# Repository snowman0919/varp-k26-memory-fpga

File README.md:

# 온디바이스 sLLM을 위한 K26–Memory FPGA 후보 구조

Kria K26이 연산·제어를 맡고 외부 Memory FPGA가 다채널로 가중치를 공급하는
확장형 가속기 구조를 설계하고, 데이터 이동 비용을 포함한 작업 재분배가 언제
유효한지 평가한 연구 저장소다.

## 핵심 결론

- Gemma 3 1B INT8와 문맥 길이 32K의 용량 모델은 2.43 GiB다. 따라서 기본 선택은
  K26 로컬이며 외부 8GB는 더 큰 모델·긴 문맥·로컬 경합을 위한 확장 후보다.
- 실제 그래프의 토큰당 183개 투영을 의존성 있는 802개 TileJob으로 변환했다.
- 합성 편향 부하의 동일 시드 다섯 개 중앙값에서 S3는 S1보다 TileJob p95를
  19.13%, p99를 18.71% 줄였다. 반면 Gemma 기존 산술 배치에서는 p95가 0.28%
  늘어 정책 효과가 초기 배치와 이동 비용에 조건부임을 확인했다.
- 대표 실제 가중치 타일 세 개가 작업 수락→DMA 요청→DDR 응답 경계→논리 링크
  FIFO→MatVec 결과의 폐루프 논리 RTL을 통과했고 INT32 기준과 일치했다.

이 수치는 보드 실측이 아니다. GTH·MIG 물리 타이밍, 전체 보드 전력·가격,
제작 가능한 PCB는 아직 검증하지 않았다.

## 연구 기여

1. K26의 연산·제어와 Memory FPGA의 가중치 공급 역할을 분리한 확장 후보 구조
2. 원격 가중치·활성값·부분합 비용을 서비스 시간에 부과한 동적 작업 배치 평가
3. 실제 모델 형상→분석 모델→폐루프 논리 RTL→KiCad 라우팅 쿠폰의 재현 흐름

## 빠른 시작

필수 도구는 Python 3.11+, Java 21, sbt, Verilator, KiCad CLI, Pandoc,
Chromium, Poppler, ffmpeg, Manim과 한글 글꼴이다.

```bash
make setup
make test
make rtl-test
make paper-experiments
make research-freeze
make paper
make presentation
make reproduce
```

허가된 원본 Gemma 3 1B ONNX가 있을 때만 다음 명령으로 trace를 재생성한다.
모델 가중치는 저장소와 release에 포함하지 않는다.

```bash
GEMMA3_1B_ONNX_DIR=/authorized/path make model-trace
```

## 주요 산출물

- [제출 논문](paper/final/submission_manuscript.pdf)
- [기술보고서](paper/technical_report/technical_report.pdf)
- [17장 본선 발표자료](presentation/final/presentation.pptx)
- [발표 PDF](presentation/final/presentation.pdf)
- [발표자 노트](presentation/final/speaker_notes.md)
- [슬라이드별 출처 인덱스](presentation/final/slide_source_index.md)
- [발표 contact sheet](presentation/final/slide_contact_sheet.png)
- [연구 동결 기록](research/v11_research_freeze.md)
- [스터디팩과 Q&A](study/README.md)
- [코드·자료 공개 안내](paper/final/code_and_data_availability.md)
- [학술대회 패키지 통합 인덱스](conference_package/INDEX.md)

## 저장소 구조

| 경로 | 내용 |
|---|---|
| `src/`, `tests/` | 의존성 인식 분석 모델과 검증 |
| `hw/` | SpinalHDL/Verilator RTL과 폐루프 논리 가상 시제품 |
| `experiments/`, `results/`, `evidence/` | Gemma trace, 합성 실험, 결과 CSV |
| `hardware/kicad/` | 일반 경계 라우팅 쿠폰, **NOT FOR FABRICATION** |
| `paper/`, `presentation/`, `study/` | 논문·발표·방어 자료 |

## 재현과 주장 범위

`make research-freeze`는 동일 시드 비교, 원격 복사 비용 부과, Gemma 단계·토큰
의존성, 실제 타일 RTL trace, K26 로컬 기준선과 KiCad 범위를 검사한다. 자세한
논리/물리 경계는 [architecture.md](docs/architecture.md)를 따른다.

## 소스 아카이브

GitHub의 자동 **Download ZIP**은 저장소 tree를 그대로 받는 편의 경로다. 재현
기준은 `v11-conference-final` release에 첨부하는 공식
`VARP_K26_Source.zip`이며, 이 파일은 `source_manifest`와 checksum을 함께
포함한다. 두 경로 모두 모델 가중치는 포함하지 않는다.

## 인용과 라이선스

[CITATION.cff](CITATION.cff)의 최윤혁(한국디지털미디어고등학교,
[ORCID 0009-0006-3537-0249](https://orcid.org/0009-0006-3537-0249)) 정보를 사용한다.
소스 사용 조건은 [LICENSE](LICENSE)를 따른다.

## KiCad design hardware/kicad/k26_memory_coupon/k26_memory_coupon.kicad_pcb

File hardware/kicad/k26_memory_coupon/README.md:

# K26 memory/interface validation coupon

> **NOT FOR FABRICATION — proposal_only**

This electrically connected KiCad 9 coupon accounts for one DDR3L x16
representative channel slice, a four-lane full-duplex K26 PL-GTH link bundle,
two K26 GTH reference-clock inputs, reset/config/JTAG, and a decoupling subset.

The XC7K160T and K26 are connector/bank boundaries. No XC7K160T FFG676 ball,
MIG placement, production stackup, impedance, or timing claim is made.

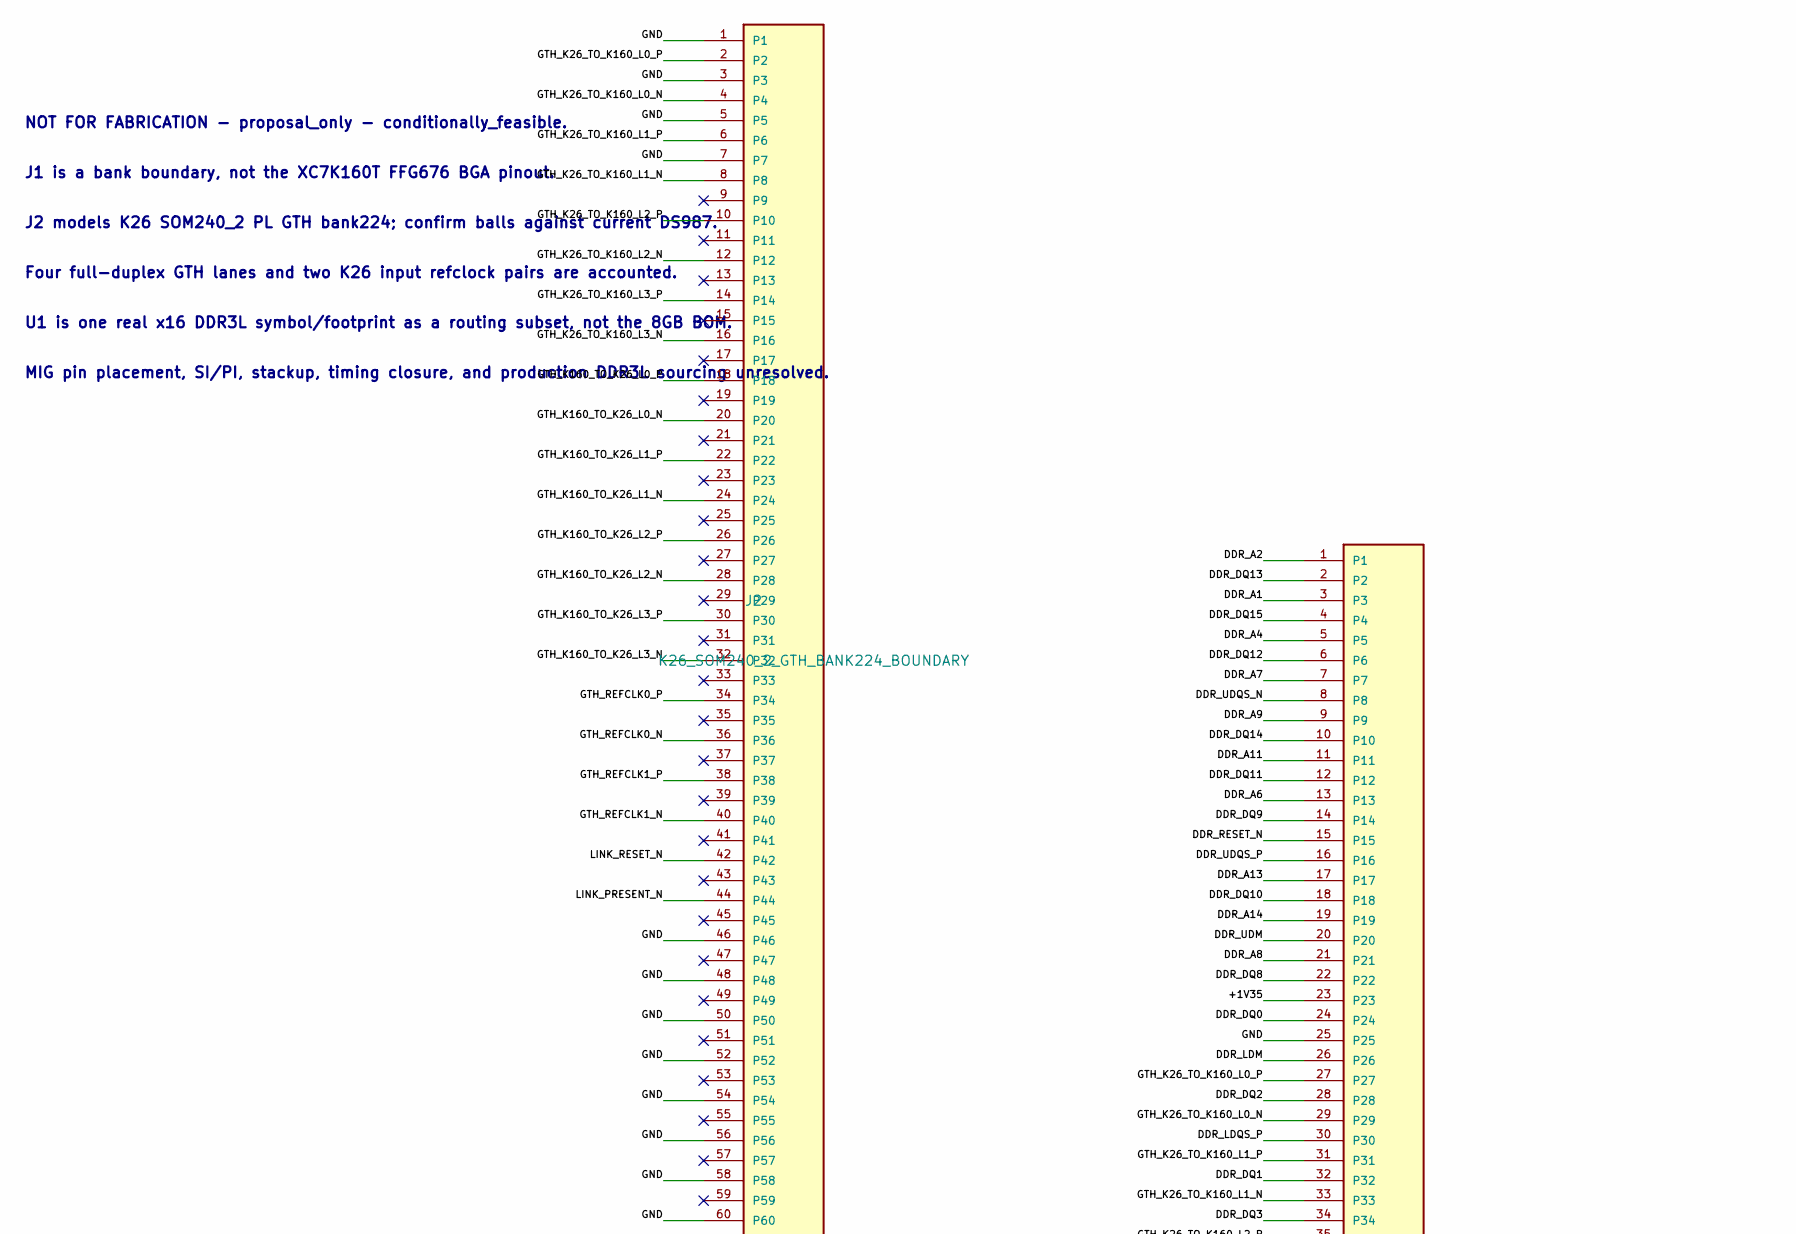
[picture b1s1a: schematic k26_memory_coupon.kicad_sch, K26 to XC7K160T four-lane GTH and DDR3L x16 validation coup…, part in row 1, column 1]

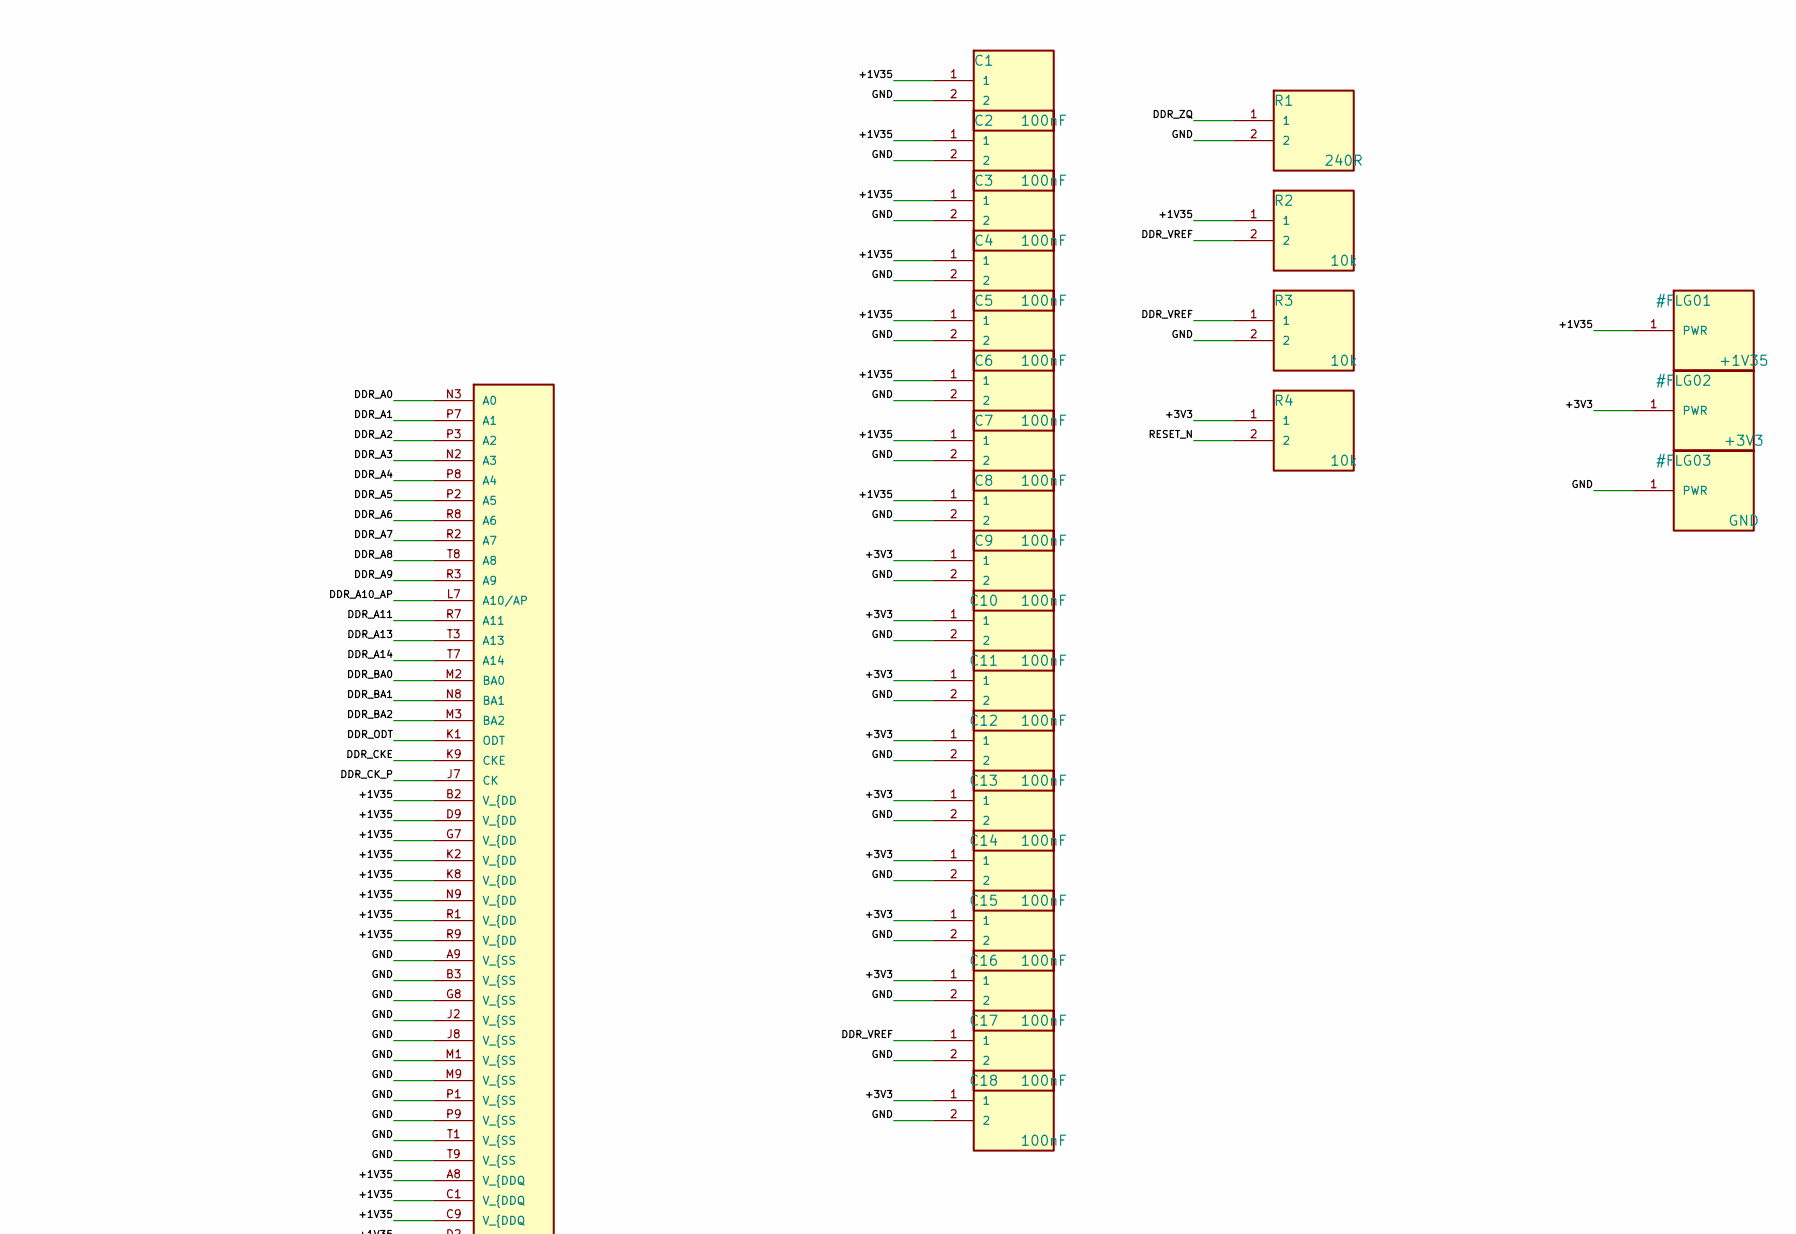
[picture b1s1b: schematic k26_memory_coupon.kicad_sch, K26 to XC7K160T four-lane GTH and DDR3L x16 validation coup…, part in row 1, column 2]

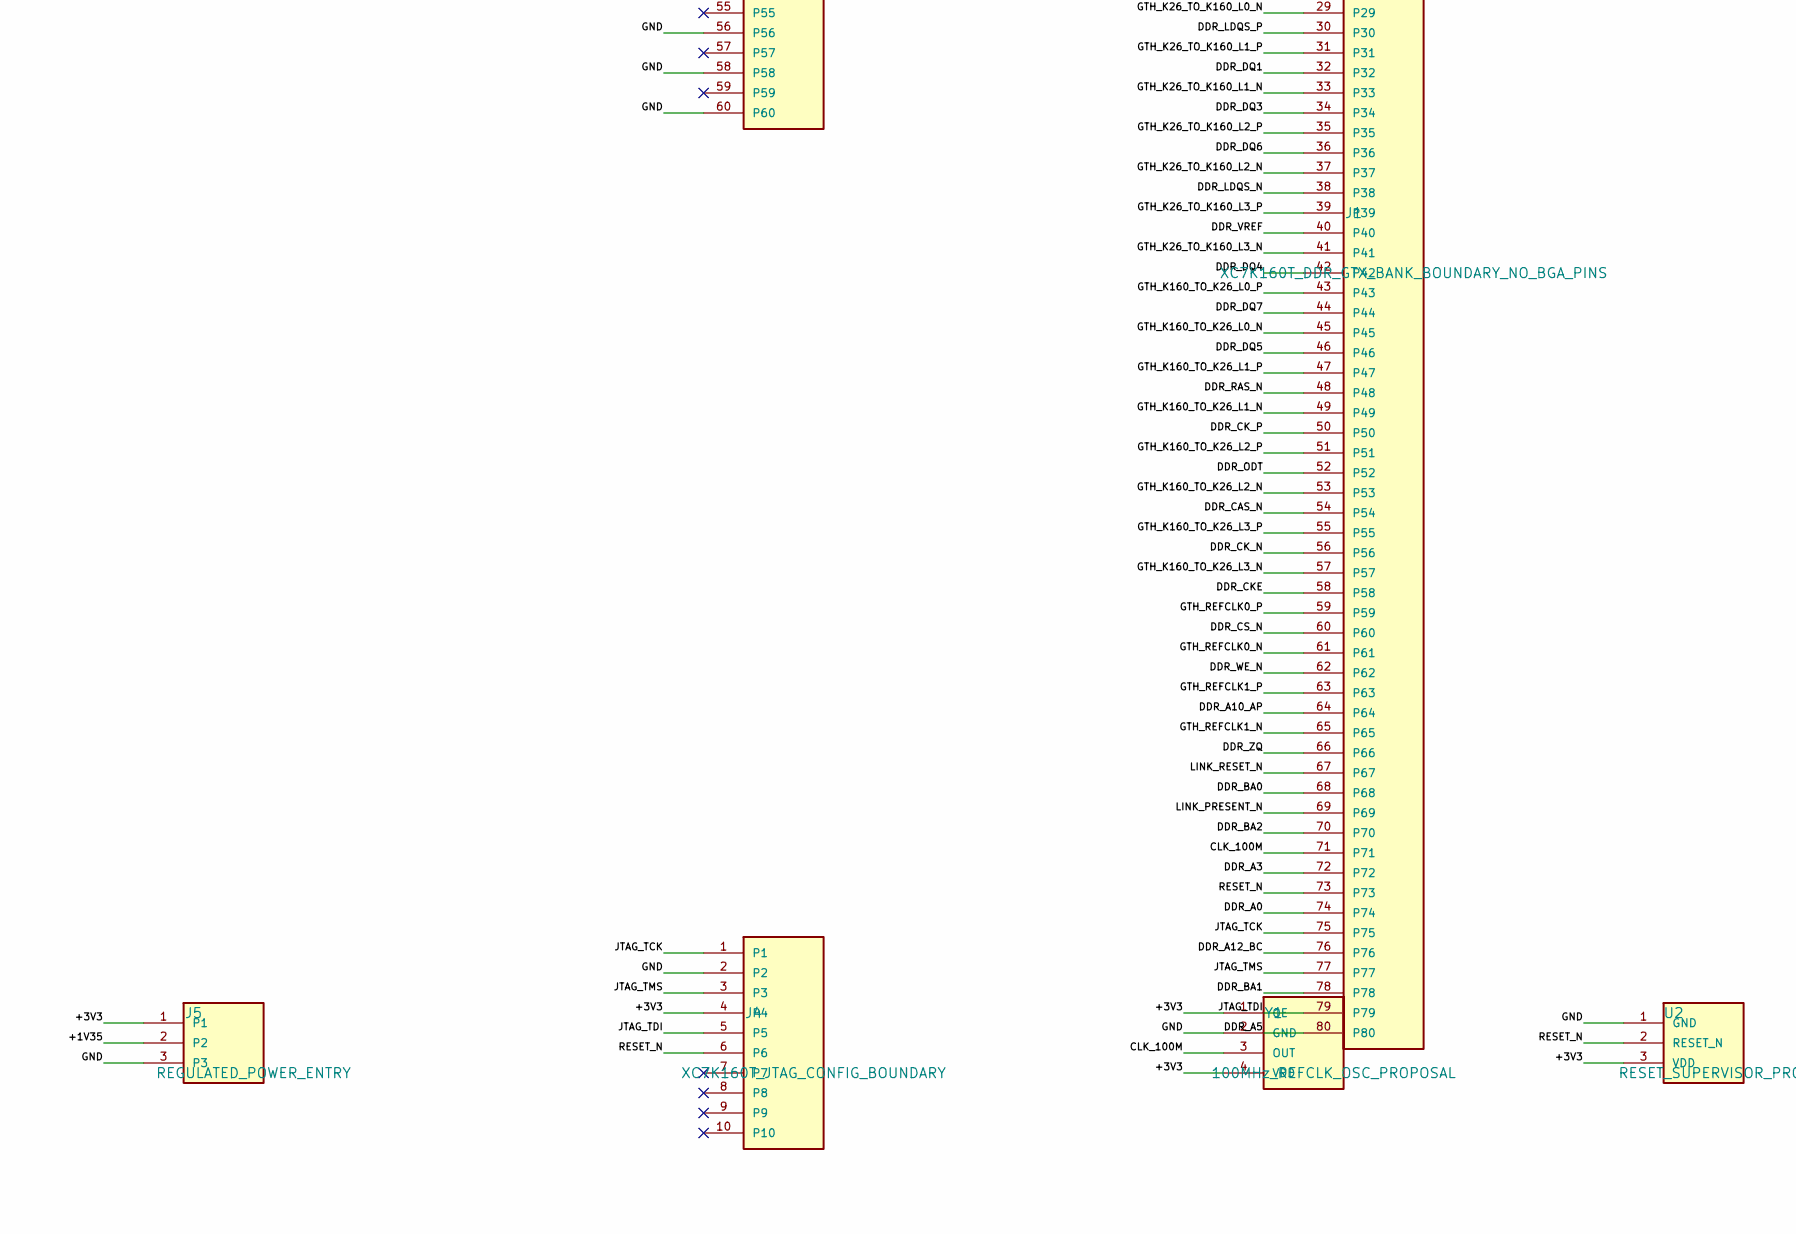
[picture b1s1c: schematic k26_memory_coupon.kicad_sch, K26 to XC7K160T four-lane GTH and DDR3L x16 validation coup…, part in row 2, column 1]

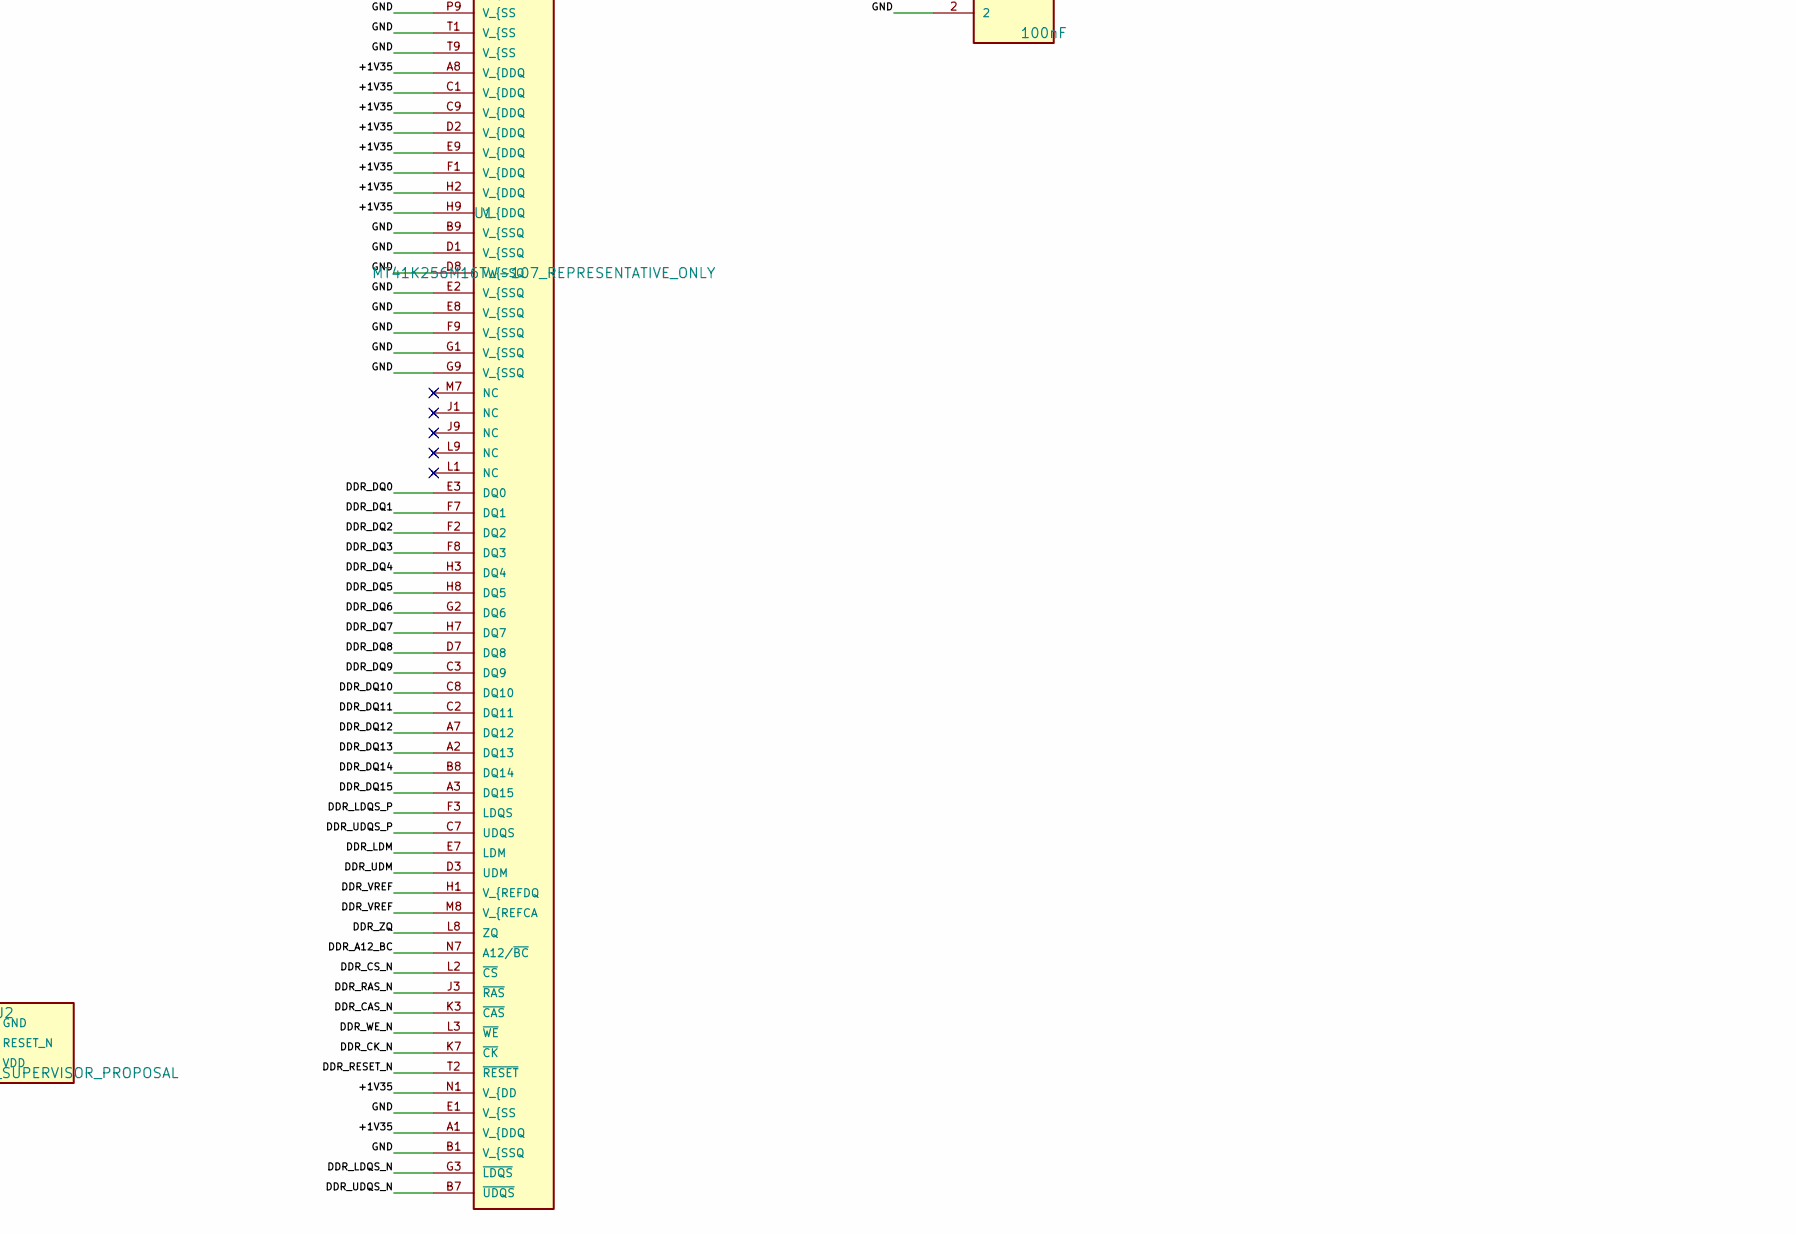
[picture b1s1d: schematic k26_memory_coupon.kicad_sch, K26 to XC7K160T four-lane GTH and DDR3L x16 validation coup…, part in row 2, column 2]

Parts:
C1, C2, C3, C4, C5, C6, C7, C8, C9, C10, C11, C12, C13, C14, C15, C16, C17, C18: 100nF; C_0402_1005Metric
J1: XC7K160T_DDR_GTX_BANK_BOUNDARY_NO_BGA_PINS; Samtec_HSEC8-140-03-X-DV_2x40_P0.8mm_Pol22_Socket
J2: K26_SOM240_2_GTH_BANK224_BOUNDARY; Samtec_HSEC8-130-03-X-DV_2x30_P0.8mm_Socket
J4: XC7K160T_JTAG_CONFIG_BOUNDARY; PinHeader_2x05_P1.27mm_Vertical
J5: REGULATED_POWER_ENTRY; TerminalBlock_Phoenix_MKDS-1,5-3_1x03_P5.00mm_Horizontal
R1: 240R; R_0402_1005Metric
R2, R3, R4: 10k; R_0402_1005Metric
U1: MT41K256M16TW-107_REPRESENTATIVE_ONLY; Micron_FBGA-96_8x14mm_Layout9x16_P0.8mm; MPN MT41K256M16TW-107
U2: RESET_SUPERVISOR_PROPOSAL; SOT-23
Y1: 100MHz_REFCLK_OSC_PROPOSAL; Oscillator_SMD_ECS_2520MV-xxx-xx-4Pin_2.5x2.0mm

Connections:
/+1V35: C1.1, C2.1, C3.1, C4.1, C5.1, C6.1, C7.1, C8.1, J1.23, J5.2, R2.1, U1.A1 (V_{DDQ), U1.A8 (V_{DDQ), U1.B2 (V_{DD), U1.C1 (V_{DDQ), U1.C9 (V_{DDQ), U1.D2 (V_{DDQ), U1.D9 (V_{DD), U1.E9 (V_{DDQ), U1.F1 (V_{DDQ), U1.G7 (V_{DD), U1.H2 (V_{DDQ), U1.H9 (V_{DDQ), U1.K2 (V_{DD), U1.K8 (V_{DD), U1.N1 (V_{DD), U1.N9 (V_{DD), U1.R1 (V_{DD), U1.R9 (V_{DD)
/+3V3: C9.1, C10.1, C11.1, C12.1, C13.1, C14.1, C15.1, C16.1, C18.1, J4.4, J5.1, R4.1, U2.3 (VDD), Y1.1 (OE), Y1.4 (VDD)
/CLK_100M: J1.71, Y1.3 (OUT)
/DDR_A0: J1.74, U1.N3 (A0)
/DDR_A1: J1.3, U1.P7 (A1)
/DDR_A2: J1.1, U1.P3 (A2)
/DDR_A3: J1.72, U1.N2 (A3)
/DDR_A4: J1.5, U1.P8 (A4)
/DDR_A5: J1.80, U1.P2 (A5)
/DDR_A6: J1.13, U1.R8 (A6)
/DDR_A7: J1.7, U1.R2 (A7)
/DDR_A8: J1.21, U1.T8 (A8)
/DDR_A9: J1.9, U1.R3 (A9)
/DDR_A10_AP: J1.64, U1.L7 (A10/AP)
/DDR_A11: J1.11, U1.R7 (A11)
/DDR_A12_BC: J1.76, U1.N7 (A12/~BC)
/DDR_A13: J1.17, U1.T3 (A13)
/DDR_A14: J1.19, U1.T7 (A14)
/DDR_BA0: J1.68, U1.M2 (BA0)
/DDR_BA1: J1.78, U1.N8 (BA1)
/DDR_BA2: J1.70, U1.M3 (BA2)
/DDR_CAS_N: J1.54, U1.K3 (~CAS)
/DDR_CKE: J1.58, U1.K9 (CKE)
/DDR_CK_N: J1.56, U1.K7 (~CK)
/DDR_CK_P: J1.50, U1.J7 (CK)
/DDR_CS_N: J1.60, U1.L2 (~CS)
/DDR_DQ0: J1.24, U1.E3 (DQ0)
/DDR_DQ1: J1.32, U1.F7 (DQ1)
/DDR_DQ2: J1.28, U1.F2 (DQ2)
/DDR_DQ3: J1.34, U1.F8 (DQ3)
/DDR_DQ4: J1.42, U1.H3 (DQ4)
/DDR_DQ5: J1.46, U1.H8 (DQ5)
/DDR_DQ6: J1.36, U1.G2 (DQ6)
/DDR_DQ7: J1.44, U1.H7 (DQ7)
/DDR_DQ8: J1.22, U1.D7 (DQ8)
/DDR_DQ9: J1.14, U1.C3 (DQ9)
/DDR_DQ10: J1.18, U1.C8 (DQ10)
/DDR_DQ11: J1.12, U1.C2 (DQ11)
/DDR_DQ12: J1.6, U1.A7 (DQ12)
/DDR_DQ13: J1.2, U1.A2 (DQ13)
/DDR_DQ14: J1.10, U1.B8 (DQ14)
/DDR_DQ15: J1.4, U1.A3 (DQ15)
/DDR_LDM: J1.26, U1.E7 (LDM)
/DDR_LDQS_N: J1.38, U1.G3 (~LDQS)
/DDR_LDQS_P: J1.30, U1.F3 (LDQS)
/DDR_ODT: J1.52, U1.K1 (ODT)
/DDR_RAS_N: J1.48, U1.J3 (~RAS)
/DDR_RESET_N: J1.15, U1.T2 (~RESET)
/DDR_UDM: J1.20, U1.D3 (UDM)
/DDR_UDQS_N: J1.8, U1.B7 (~UDQS)
/DDR_UDQS_P: J1.16, U1.C7 (UDQS)
/DDR_VREF: C17.1, J1.40, R2.2, R3.1, U1.H1 (V_{REFDQ), U1.M8 (V_{REFCA)
/DDR_WE_N: J1.62, U1.L3 (~WE)
/DDR_ZQ: J1.66, R1.1, U1.L8 (ZQ)
/GND: C1.2, C2.2, C3.2, C4.2, C5.2, C6.2, C7.2, C8.2, C9.2, C10.2, C11.2, C12.2, C13.2, C14.2, C15.2, C16.2, C17.2, C18.2, J1.25, J2.1, J2.3, J2.5, J2.7, J2.46, J2.48, J2.50, J2.52, J2.54, J2.56, J2.58, J2.60, J4.2, J5.3, R1.2, R3.2, U1.A9 (V_{SS), U1.B1 (V_{SSQ), U1.B3 (V_{SS), U1.B9 (V_{SSQ), U1.D1 (V_{SSQ), U1.D8 (V_{SSQ), U1.E1 (V_{SS), U1.E2 (V_{SSQ), U1.E8 (V_{SSQ), U1.F9 (V_{SSQ), U1.G1 (V_{SSQ), U1.G8 (V_{SS), U1.G9 (V_{SSQ), U1.J2 (V_{SS), U1.J8 (V_{SS), U1.M1 (V_{SS), U1.M9 (V_{SS), U1.P1 (V_{SS), U1.P9 (V_{SS), U1.T1 (V_{SS), U1.T9 (V_{SS), U2.1 (GND), Y1.2 (GND)
/GTH_K26_TO_K160_L0_N: J1.29, J2.4
/GTH_K26_TO_K160_L0_P: J1.27, J2.2
/GTH_K26_TO_K160_L1_N: J1.33, J2.8
/GTH_K26_TO_K160_L1_P: J1.31, J2.6
/GTH_K26_TO_K160_L2_N: J1.37, J2.12
/GTH_K26_TO_K160_L2_P: J1.35, J2.10
/GTH_K26_TO_K160_L3_N: J1.41, J2.16
/GTH_K26_TO_K160_L3_P: J1.39, J2.14
/GTH_K160_TO_K26_L0_N: J1.45, J2.20
/GTH_K160_TO_K26_L0_P: J1.43, J2.18
/GTH_K160_TO_K26_L1_N: J1.49, J2.24
/GTH_K160_TO_K26_L1_P: J1.47, J2.22
/GTH_K160_TO_K26_L2_N: J1.53, J2.28
/GTH_K160_TO_K26_L2_P: J1.51, J2.26
/GTH_K160_TO_K26_L3_N: J1.57, J2.32
/GTH_K160_TO_K26_L3_P: J1.55, J2.30
/GTH_REFCLK0_N: J1.61, J2.36
/GTH_REFCLK0_P: J1.59, J2.34
/GTH_REFCLK1_N: J1.65, J2.40
/GTH_REFCLK1_P: J1.63, J2.38
/JTAG_TCK: J1.75, J4.1
/JTAG_TDI: J1.79, J4.5
/JTAG_TMS: J1.77, J4.3
/LINK_PRESENT_N: J1.69, J2.44
/LINK_RESET_N: J1.67, J2.42
/RESET_N: J1.73, J4.6, R4.2, U2.2 (RESET_N)

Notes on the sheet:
Four full-duplex GTH lanes and two K26 input refclock pairs are accounted.
J1 is a bank boundary, not the XC7K160T FFG676 BGA pinout.
J2 models K26 SOM240_2 PL GTH bank224; confirm balls against current DS987.
NOT FOR FABRICATION - proposal_only - conditionally_feasible.
U1 is one real x16 DDR3L symbol/footprint as a routing subset, not the 8GB BOM.
MIG pin placement, SI/PI, stackup, timing closure, and production DDR3L sourcing unresolved.

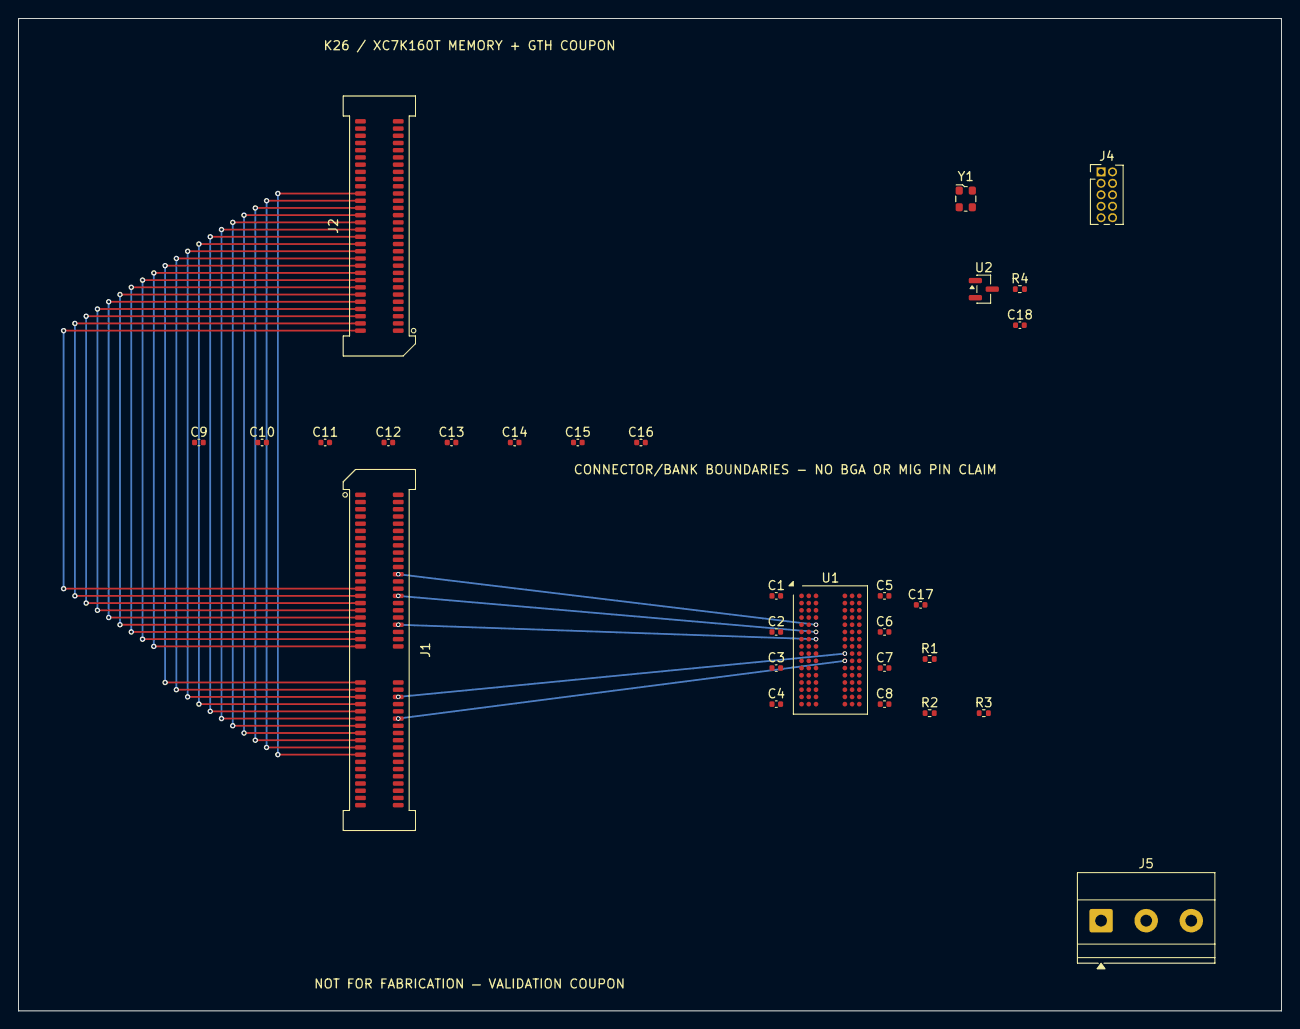
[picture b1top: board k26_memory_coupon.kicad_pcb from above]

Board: 4 copper layers, 140.0 x 110.0 mm, 29 parts (0 on the bottom side), 81 nets.
